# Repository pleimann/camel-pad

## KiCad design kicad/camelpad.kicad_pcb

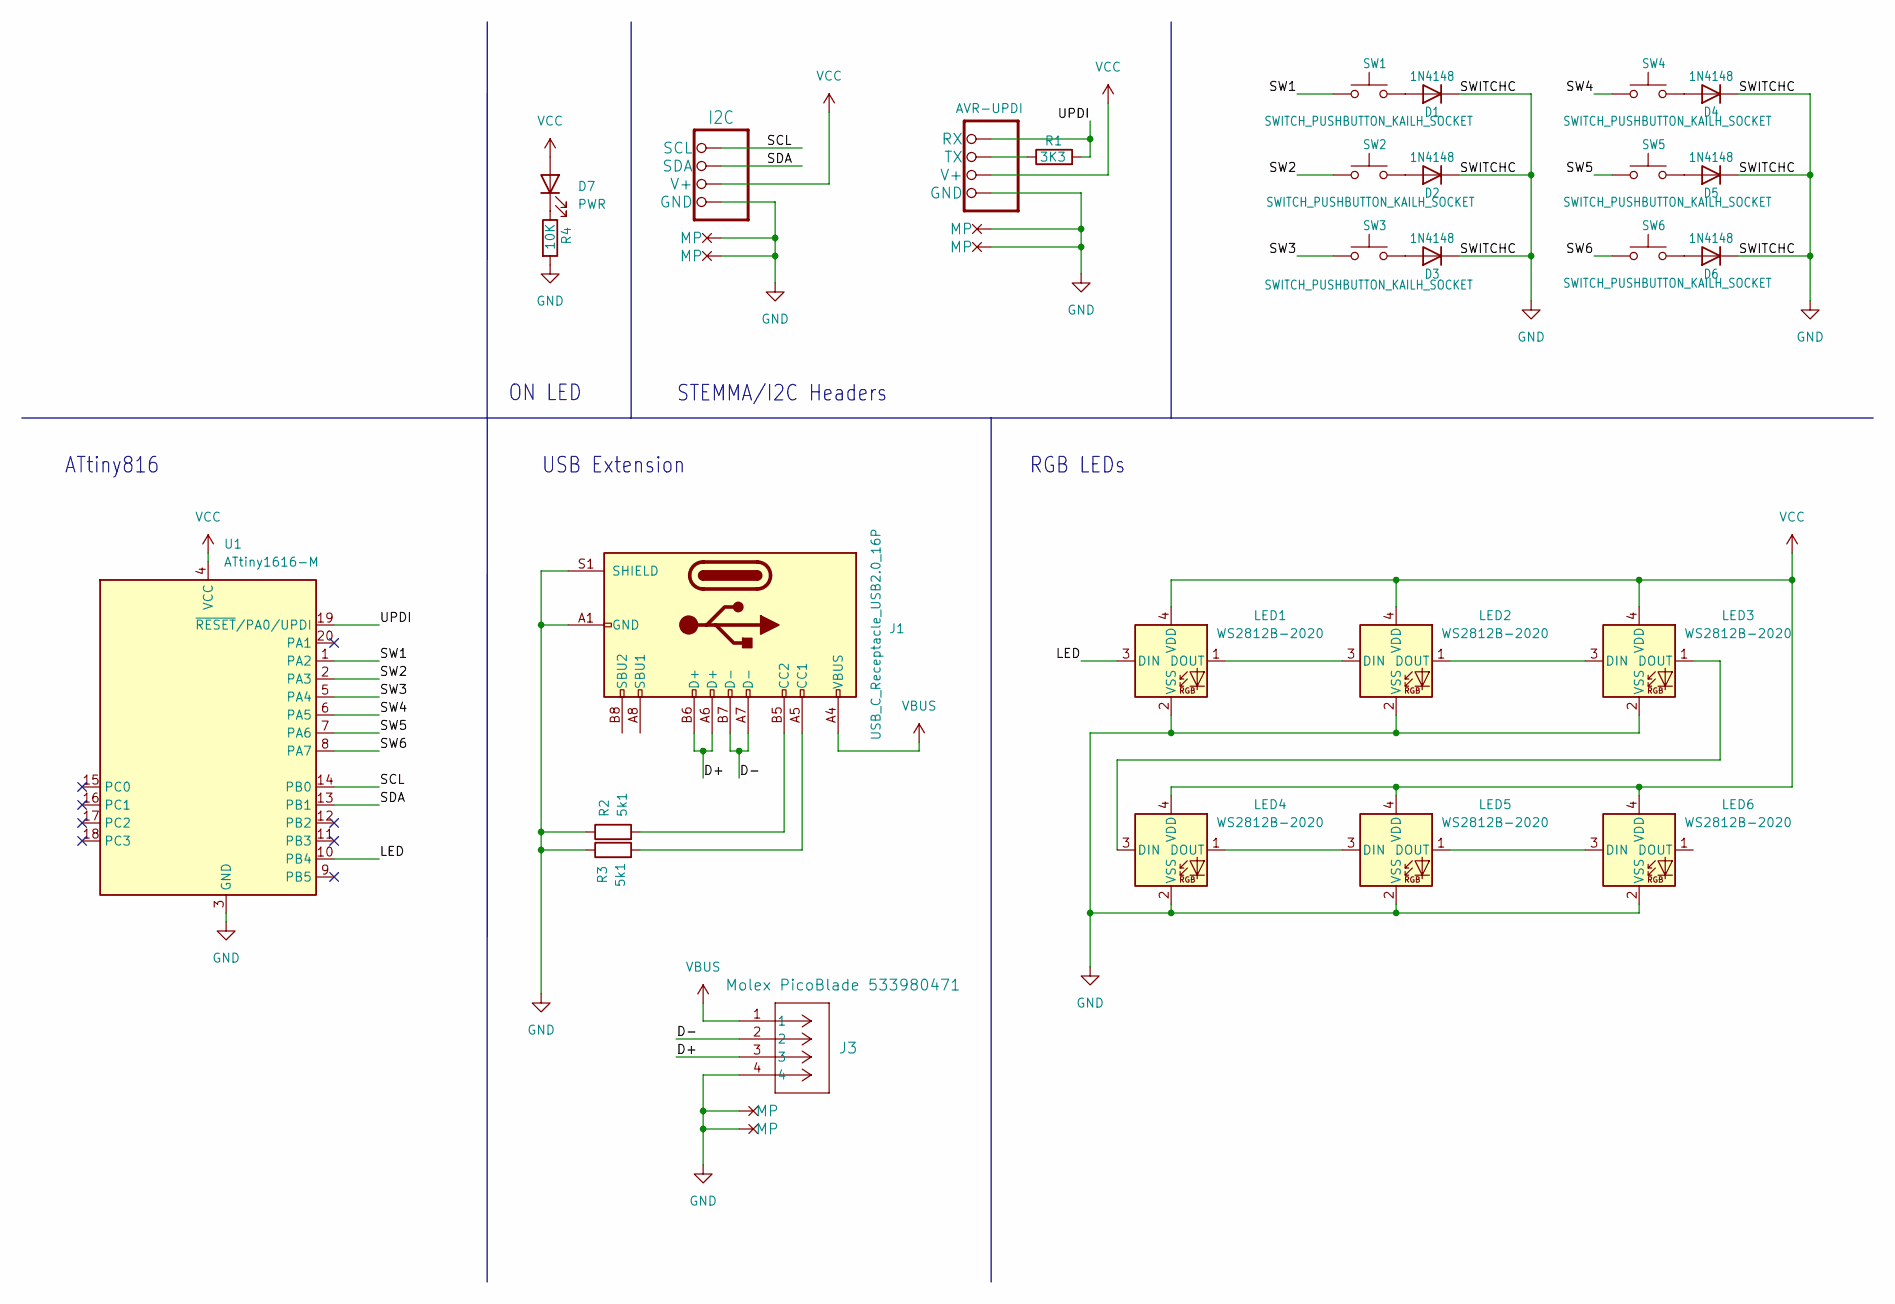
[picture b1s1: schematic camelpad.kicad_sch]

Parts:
D1, D2, D3, D4, D5, D6: 1N4148; SOD-323_L1.8-W1.3-LS2.5-RD
D7: PWR; LED_0603_1608Metric_Pad1.05x0.95mm_HandSolder
I2C1: I2C; JST_SH_BM04B-SRSS-TB_1x04-1MP_P1.00mm_Vertical
J1: USB_C_Receptacle_USB2.0_16P; USB_C_Receptacle_Palconn_UTC16-G
J3: Molex PicoBlade 533980471; CONN_53398_04_MOL
LED1, LED2, LED3, LED4, LED5, LED6: WS2812B-2020; LED-SMD_4P-L2.0-W2.0-TL_WS2812B-2020
R1: 3K3; R0603
R2, R3: 5k1; R0603
R4: 10K; R0603
SW1, SW2, SW3, SW4, SW5, SW6: SWITCH_PUSHBUTTON_KAILH_SOCKET; KAILH_SOCKET
U1: ATtiny1616-M; QFN-20_L3.0-W3.0-P0.40-BL-EP1.7
UPDI1: AVR-UPDI; JST_SH_BM04B-SRSS-TB_1x04-1MP_P1.00mm_Vertical

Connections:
/D+: J1.A6 (D+), J1.B6 (D+), J3.3
/D-: J1.A7 (D-), J1.B7 (D-), J3.2
/LED: LED1.3 (DIN), U1.10 (PB4)
/SCL: I2C1.4 (SCL), U1.14 (PB0)
/SDA: I2C1.3 (SDA), U1.13 (PB1)
/SW1: SW1.2, U1.1 (PA2)
/SW2: SW2.2, U1.2 (PA3)
/SW3: SW3.2, U1.5 (PA4)
/SW4: SW4.2, U1.6 (PA5)
/SW5: SW5.2, U1.7 (PA6)
/SW6: SW6.2, U1.8 (PA7)
/UPDI: R1.2, U1.19 (~RESET/PA0/UPDI), UPDI1.4 (RX)
GND: D1.1 (K), D2.1 (K), D3.1 (K), D4.1 (K), D5.1 (K), D6.1 (K), I2C1.1 (GND), I2C1.5 (MP), I2C1.6 (MP), J1.A1 (GND), J1.A12 (GND), J1.B1 (GND), J1.B12 (GND), J1.S1 (SHIELD), J3.4, J3.5 (MP), J3.6 (MP), LED1.2 (VSS), LED2.2 (VSS), LED3.2 (VSS), LED4.2 (VSS), LED5.2 (VSS), LED6.2 (VSS), R2.1, R3.1, R4.2, U1.3 (GND), UPDI1.1 (GND), UPDI1.5 (MP), UPDI1.6 (MP)
unnamed: D1.2 (A), SW1.1
unnamed: D2.2 (A), SW2.1
unnamed: D3.2 (A), SW3.1
unnamed: D4.2 (A), SW4.1
unnamed: D5.2 (A), SW5.1
unnamed: D6.2 (A), SW6.1
unnamed: D7.1 (K), R4.1
unnamed: J1.A5 (CC1), R3.2
unnamed: J1.B5 (CC2), R2.2
unnamed: LED1.1 (DOUT), LED2.3 (DIN)
unnamed: LED2.1 (DOUT), LED3.3 (DIN)
unnamed: LED3.1 (DOUT), LED4.3 (DIN)
unnamed: LED4.1 (DOUT), LED5.3 (DIN)
unnamed: LED5.1 (DOUT), LED6.3 (DIN)
unnamed: R1.1, UPDI1.3 (TX)
VBUS: J1.A4 (VBUS), J1.A9 (VBUS), J1.B4 (VBUS), J1.B9 (VBUS), J3.1
VCC: D7.2 (A), I2C1.2 (V+), LED1.4 (VDD), LED2.4 (VDD), LED3.4 (VDD), LED4.4 (VDD), LED5.4 (VDD), LED6.4 (VDD), U1.4 (VCC), UPDI1.2 (V+)

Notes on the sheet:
STEMMA/I2C Headers
ON LED
RGB LEDs
USB Extension
ATtiny816

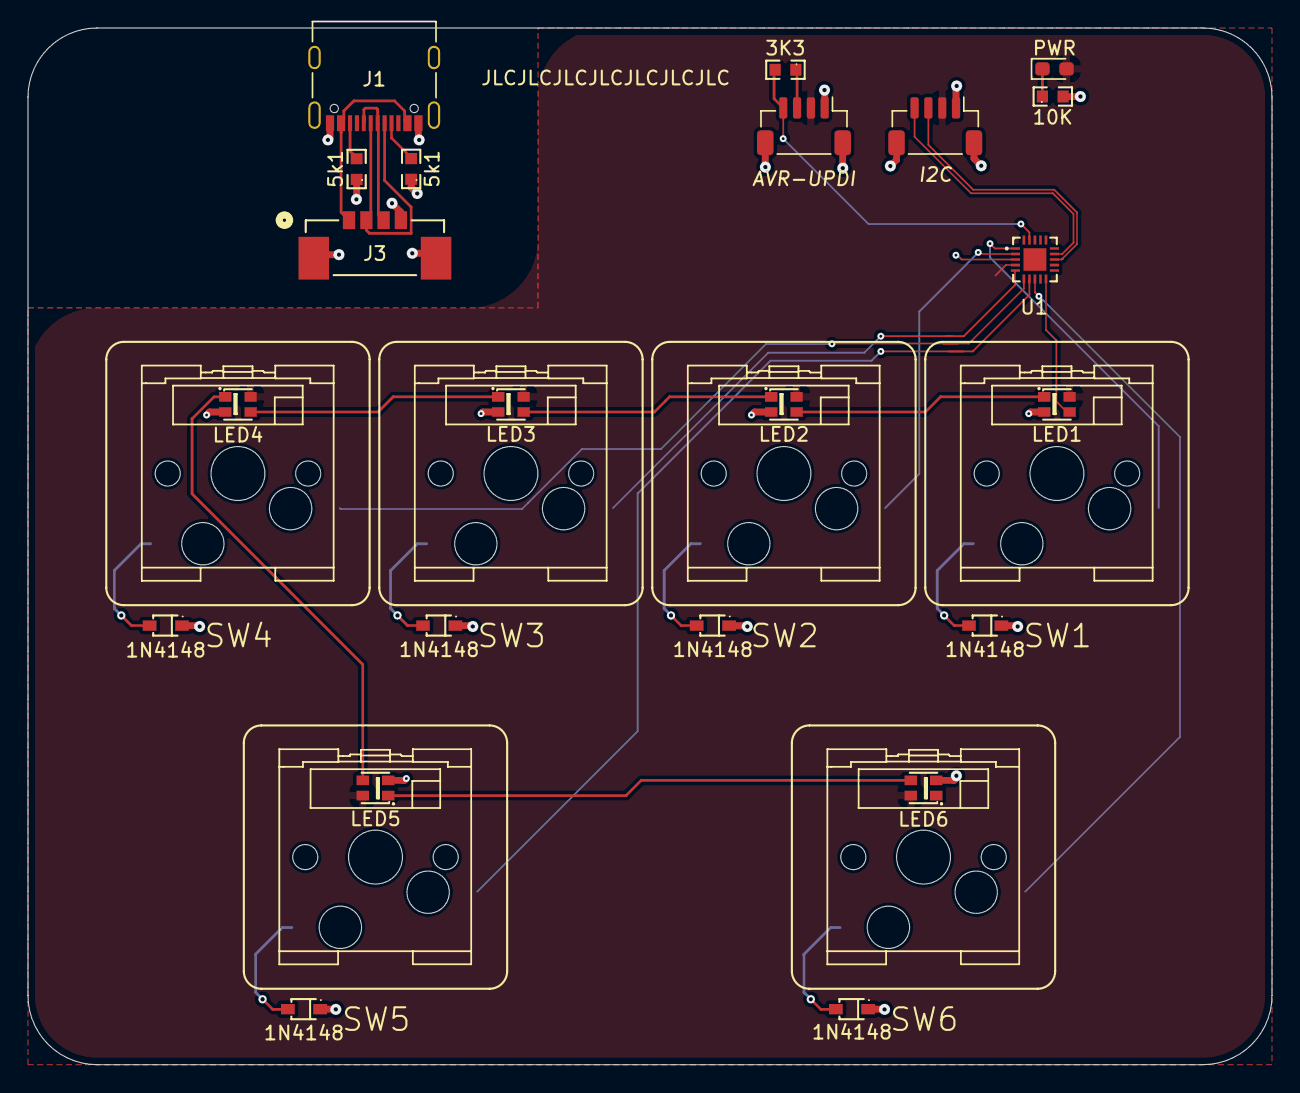
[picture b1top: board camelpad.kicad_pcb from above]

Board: 2 copper layers, 90.0 x 75.0 mm, 28 parts (0 on the bottom side), 30 nets.

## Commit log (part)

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2026-01-20 add build script
2026-01-20 Add circuitpython client for the camel-pad
2026-01-21 update build and circup scripts
2026-01-27 Add gesture detection and controller for Camel Pad; update configuration and sync scripts
2026-01-27 Add custom HID support with 10-key keyboard and host messaging
    Adds custom USB HID configuration for extended functionality:
    - boot.py: Configures custom HID descriptor at startup
    - custom_hid.py: CamelPadKeyboard (10 keycodes) and CamelPadHostReceiver classes
    - Extended keyboard IN report supports 10 simultaneous keys (vs standard 6)
    - Feature report for receiving up to 1024-byte messages from host
    - OUT report for 64-byte streaming data packets from host
2026-01-31 Convert to TS
2026-02-01 Update libraries
2026-02-03 add esphome conf
2026-02-03 Remove circuitpython program
2026-02-03 Refactor documentation and remove obsolete scripts for ESPHome integration
2026-02-06 Add platformio firmware for CamelPad with display and communication features
    - Created platformio.ini for ESP32-S3 configuration.
    - Implemented communication protocol in protocol.h for message framing and checksum.
    - Developed SerialComms class for handling serial communication and message processing.
    - Added configuration for I2C and display in config.h.
    - Implemented display initialization and management in display_manager.
    - Integrated display rendering with button labels and status notifications.
2026-02-17 display: increase status label font to 24px
2026-02-21 Enhance serial communication handling with timeout reset and improve LVGL task management
2026-02-21 Schematic Cleanup
2026-02-22 Update KiCad project
2026-02-24 Add Keybindings (Keys) tab to tray settings UI
    Adds a fourth "Keys" tab to the tray popover that lets users configure
    button-gesture-to-action mappings without editing the YAML file directly.
    - Renders 4 key cards (Key 1–4) dynamically from the loaded config
    - Each card exposes Press / Double Press / Long Press rows with Action
    and Label inputs matching the ActionMapping config schema
    - collectKeybindings() serialises the form back to Config.keys format
2026-03-11 Update usb connector to molex picoblade
2026-03-11 feat: implement AskUserQuestion and Stop hooks for enhanced user interaction
2026-03-12 feat: enhance key mapping and gesture handling with action types and simulation support
2026-03-13 feat: add app activation feature and enhance tray binary build process
2026-03-26 refactor(plugin): migrate hooks to ESM and add MCP server support
    - Convert all hook scripts from CommonJS to ES modules
    - Add .mcp.json to expose camel-pad as MCP server via bun
    - Add @modelcontextprotocol/sdk, yaml, zod dependencies
    - Add server.ts as MCP server entry point
    - Rename mise task `run` to `dev`
2026-03-26 Bump requests in /firmware in the uv group across 1 directory
    Bumps the uv group with 1 update in the /firmware directory: [requests](https://github.com/psf/requests).
    Updates `requests` from 2.32.5 to 2.33.0
    - [Release notes](https://github.com/psf/requests/releases)
    - [Changelog](https://github.com/psf/requests/blob/main/HISTORY.md)
    - [Commits](https://github.com/psf/requests/compare/v2.32.5...v2.33.0)
    ---
2026-03-27 Bump yaml in /plugin in the npm_and_yarn group across 1 directory
    Bumps the npm_and_yarn group with 1 update in the /plugin directory: [yaml](https://github.com/eemeli/yaml).
    Updates `yaml` from 2.8.2 to 2.8.3
    - [Release notes](https://github.com/eemeli/yaml/releases)
    - [Commits](https://github.com/eemeli/yaml/compare/v2.8.2...v2.8.3)
    ---
    updated-dependencies:
2026-03-28 chore: update dependencies and enhance logging in hook scripts
2026-03-29 Update design rules and component footprints in camelpad project
    - Added multiple DRC exclusions for silk and copper layers in camelpad.kicad_pro to improve layout integrity.
    - Adjusted solder mask to copper clearance from 0.0 to 0.005 for better manufacturing tolerance.
    - Updated component footprints in camelpad.kicad_sch from 0402 to 0603 for resistors and capacitors to accommodate new specifications.
    - Changed LED footprint to a specific camelpad variant for improved compatibility.
    - Modified resistor array footprints from 4x0603 to 4x1206 to reflect updated design requirements.
2026-03-31 Remove LDO as it's not needed. Clean 3v3 power comes from the controller
